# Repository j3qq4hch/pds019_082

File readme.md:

# PDS019_082

В этом репозитории лежат исходники устройства PDS019_082. Это контроллер, управляющий состоянием плавательного бассейна. 
Внешний вид представлен на картинке ниже:

> [!IMPORTANT]
> Исходная документация (включая производственную документацию) хранится [здесь](https://github.com/j3qq4hch/pds019_082/issues/1).

3d модель доступна [по ссылке](https://a360.co/41i2nmS).

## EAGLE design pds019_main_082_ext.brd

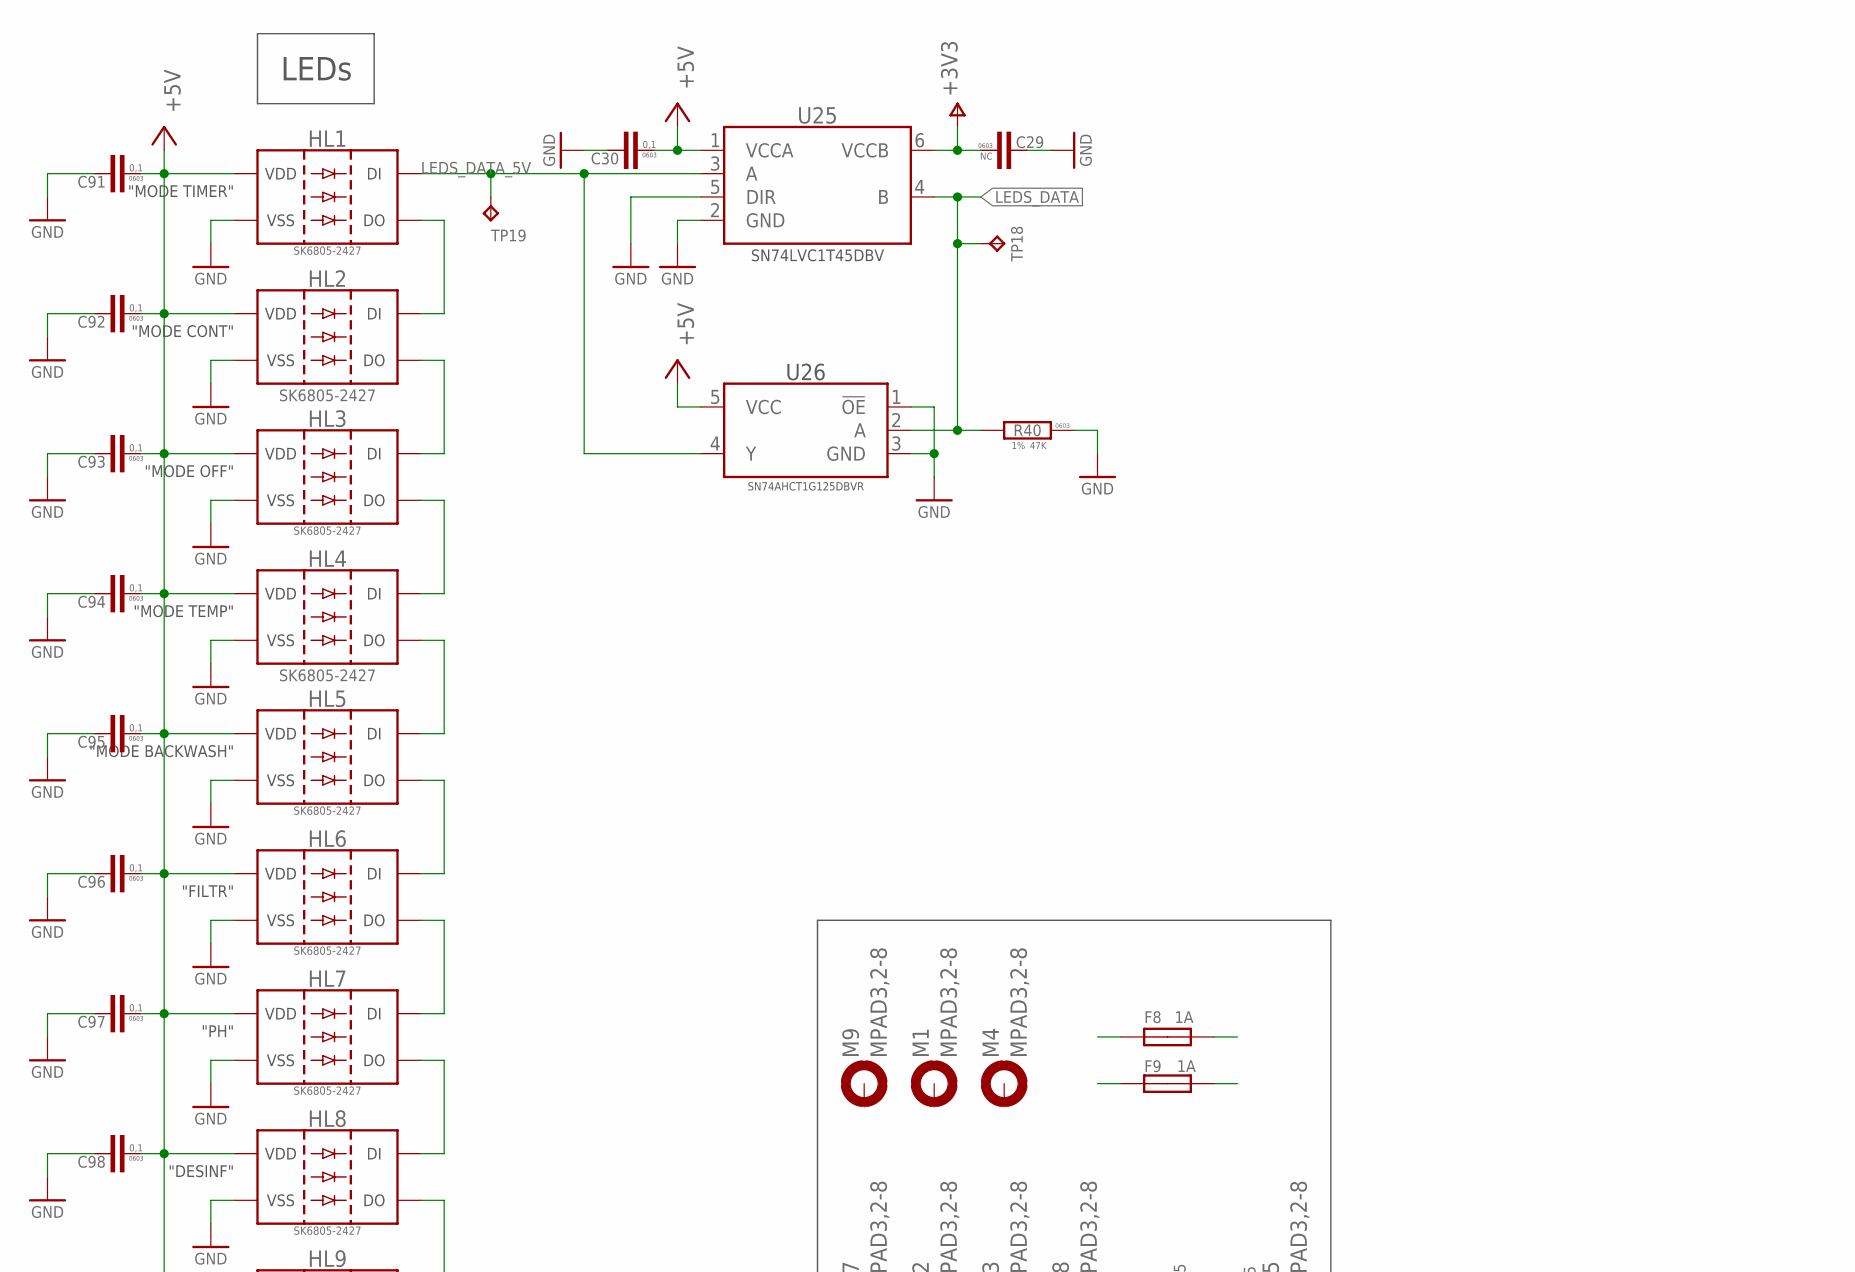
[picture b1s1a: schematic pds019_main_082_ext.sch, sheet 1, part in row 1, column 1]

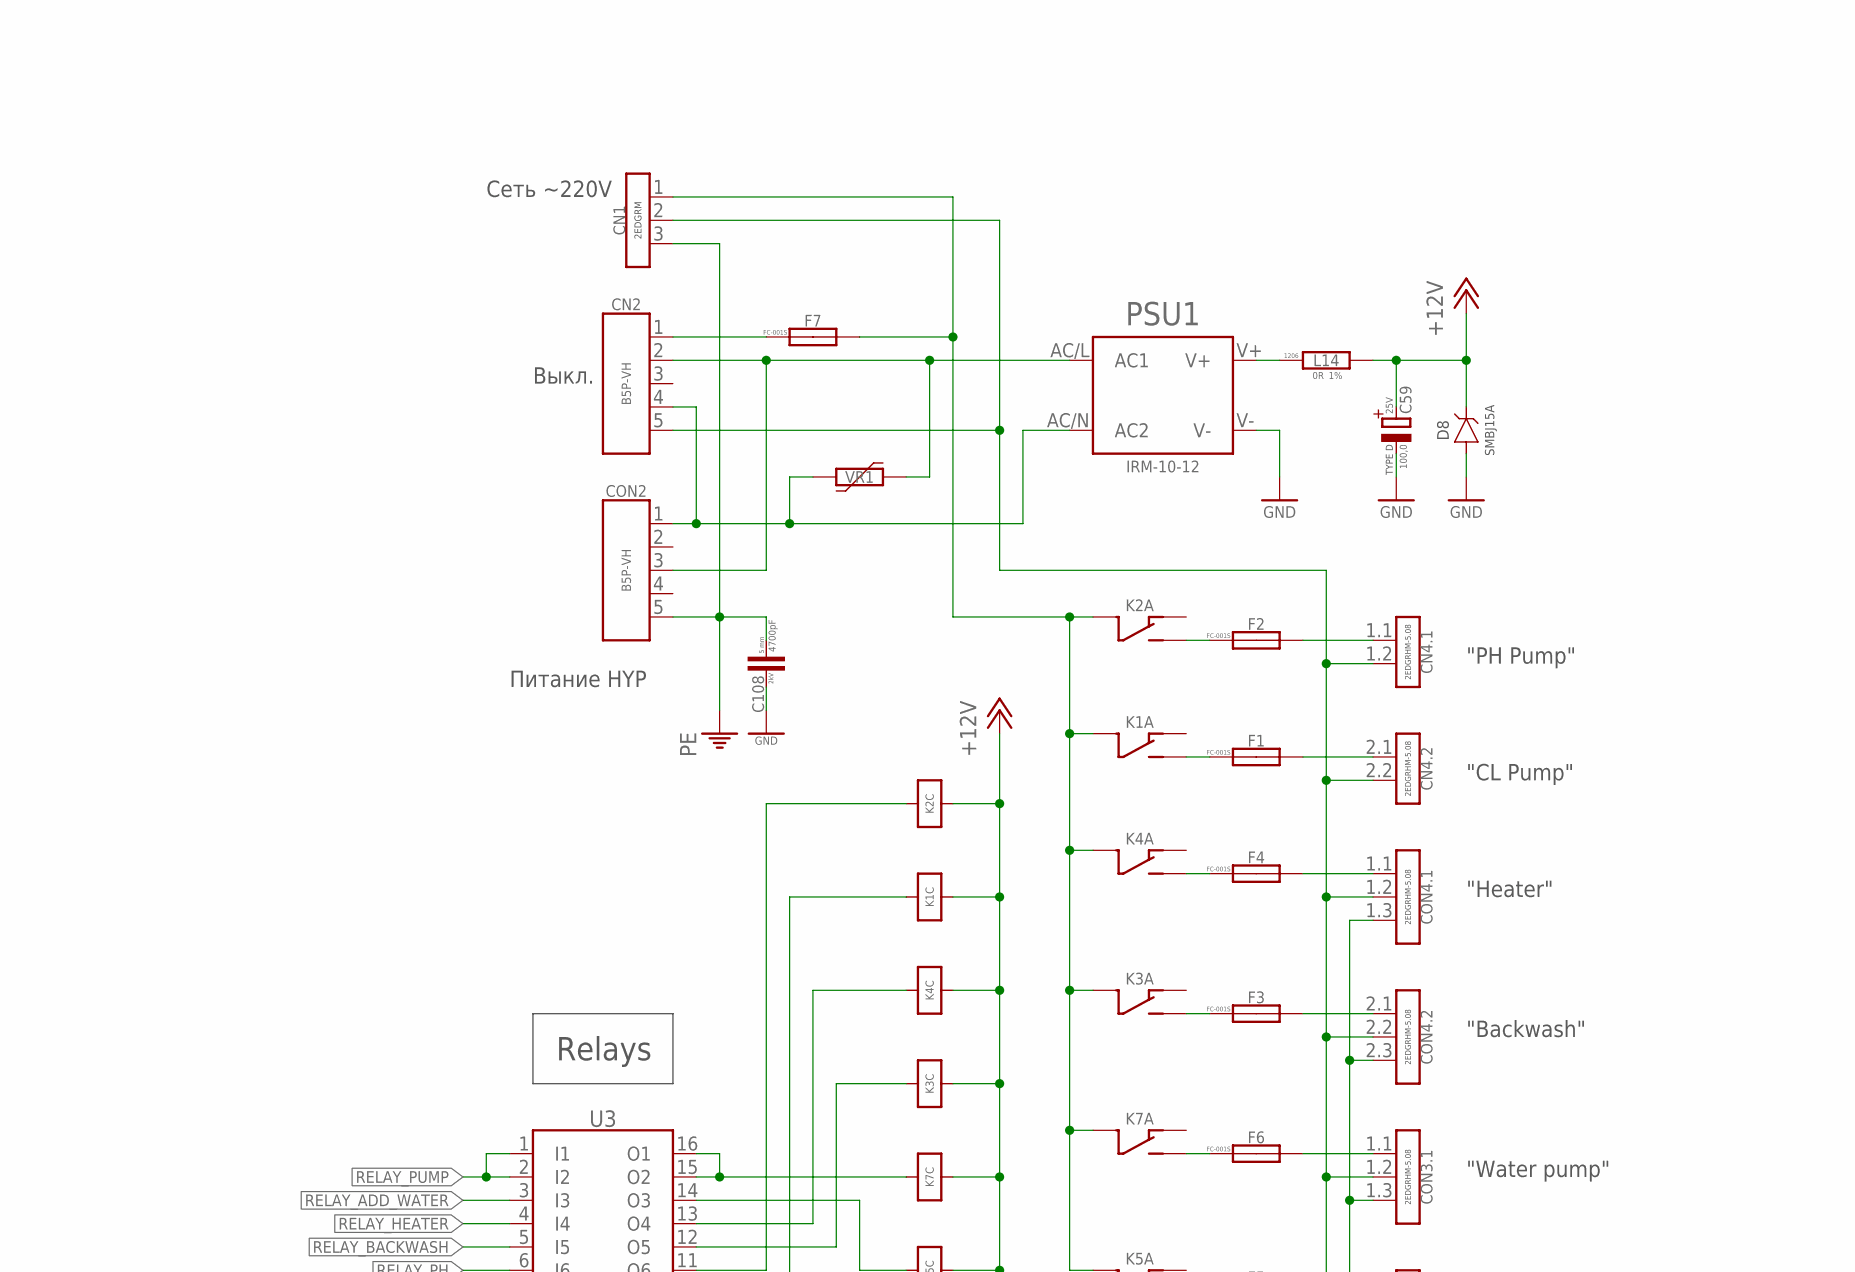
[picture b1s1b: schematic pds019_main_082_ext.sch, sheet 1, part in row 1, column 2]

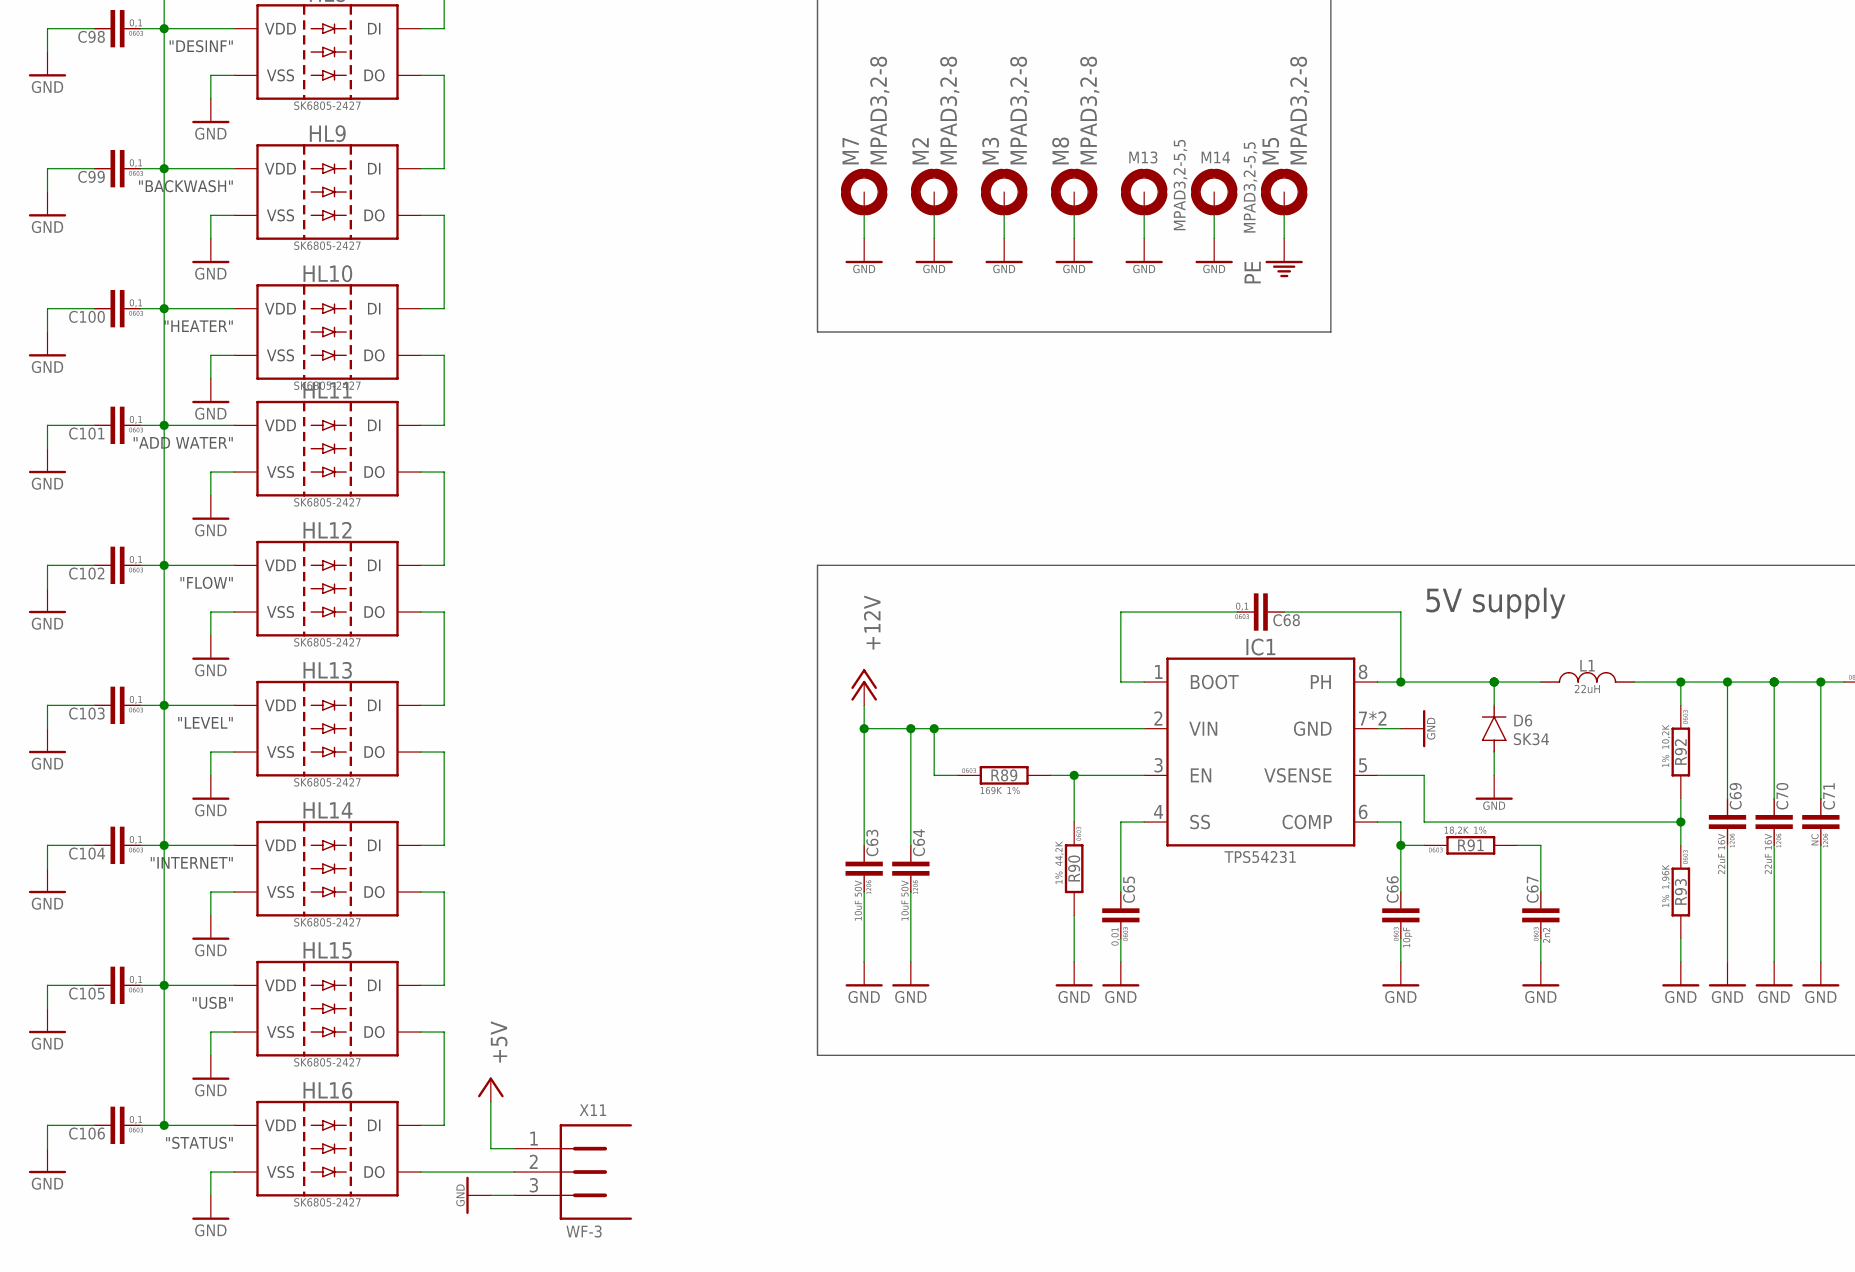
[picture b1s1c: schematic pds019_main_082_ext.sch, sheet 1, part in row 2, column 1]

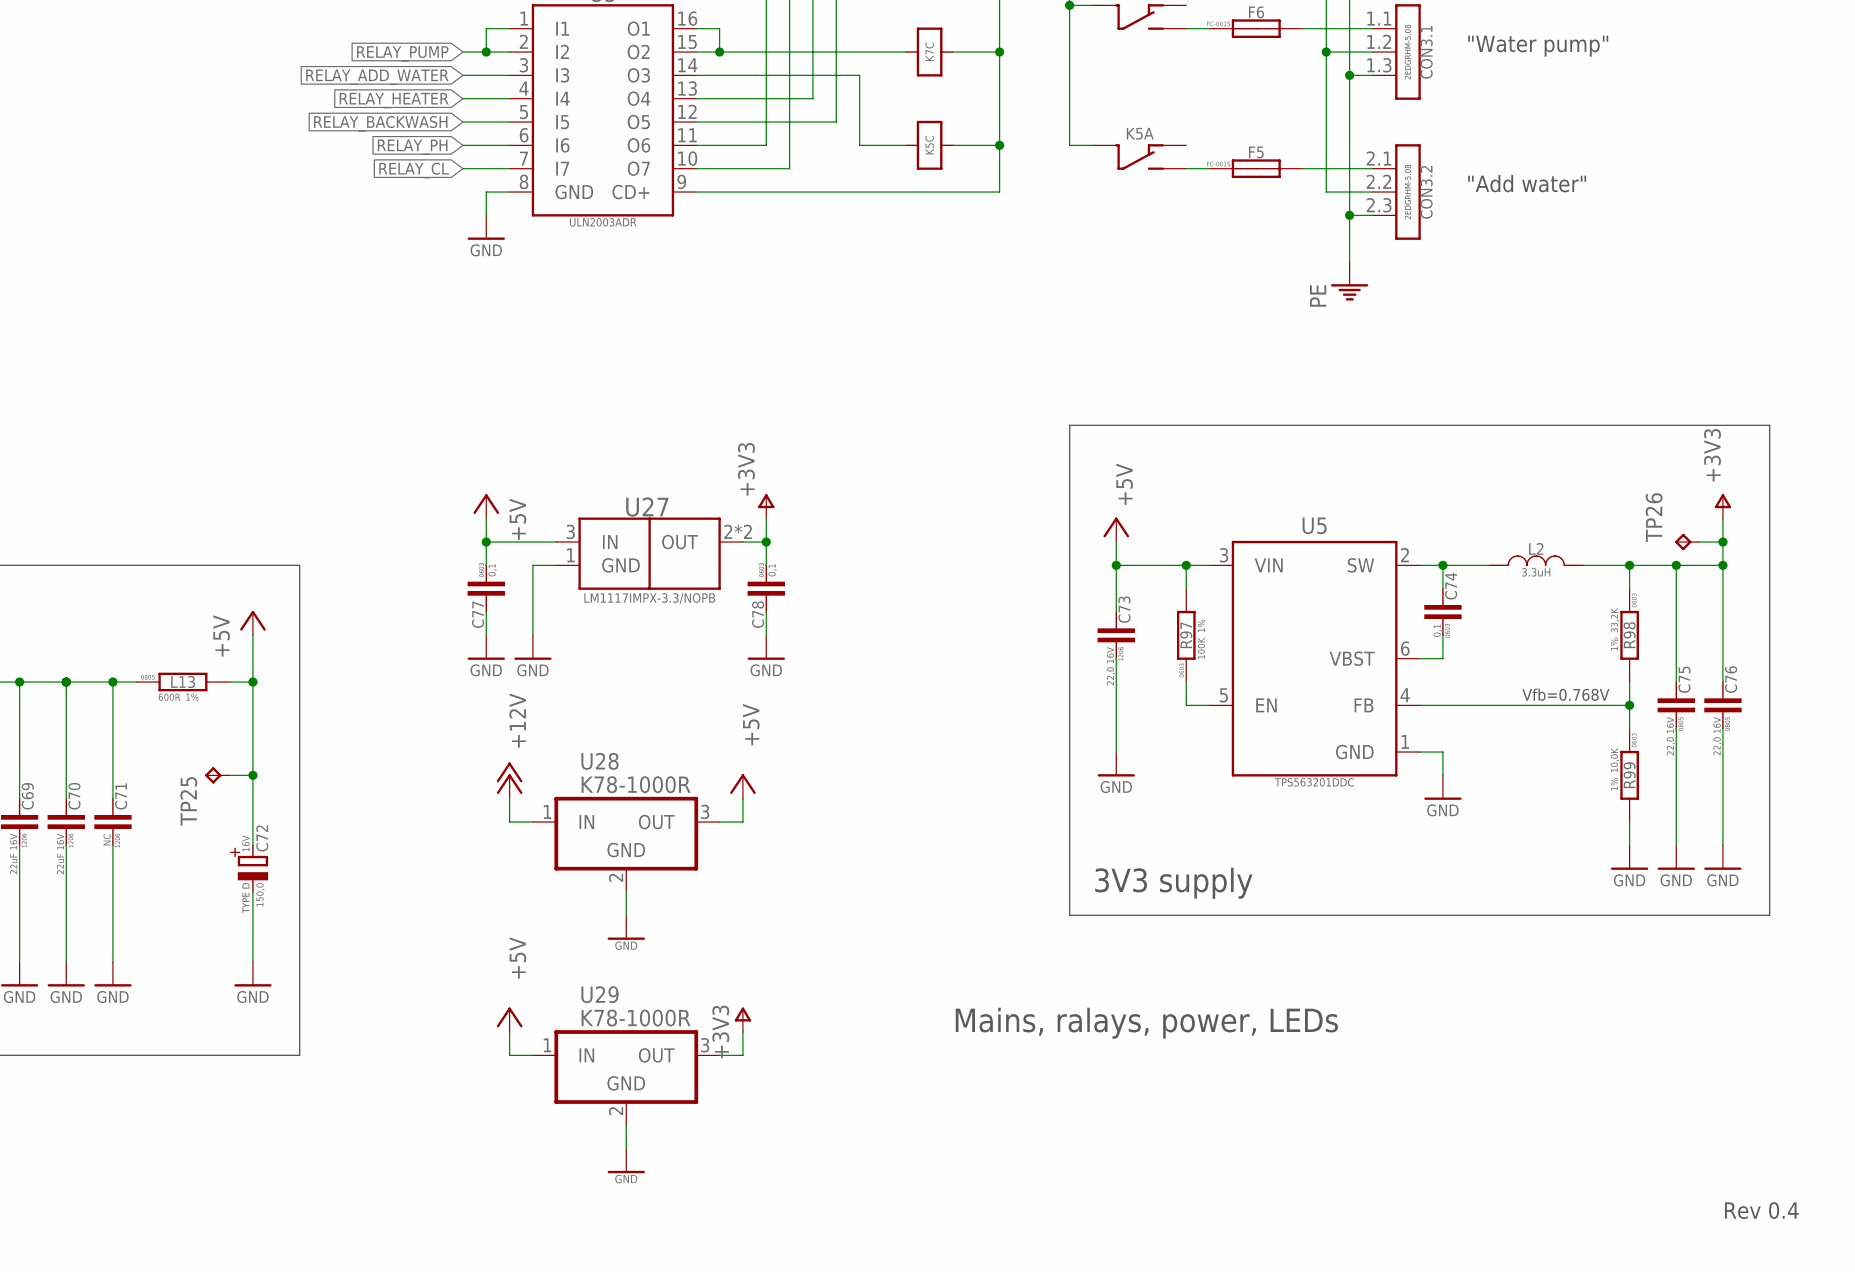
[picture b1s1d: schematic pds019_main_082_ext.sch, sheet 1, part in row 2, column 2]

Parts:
C29: NC; C0603
C30, C68, C74, C77, C78, C91, C92, C93, C94, C95, C96, C97, C98, C99, C100, C101, C102, C103, C104, C105, C106: 0,1; C0603
C59: 100,0; CTANT_7X4; VOLTAGE 25V
C63, C64: 10uF 50V; C1206
C65: 0,01; C0603
C66: 10pF; C0603
C67: 2n2; C0603
C69, C70: 22uF 16V; C1206
C71: NC; C1206
C72: 150,0; CTANT_7X4; VOLTAGE 16V
C73: 22,0 16V; C1206
C75, C76: 22,0 16V; C0805
C108: 4700pF; C_5MM; VOLTAGE 2kV
CN1: 2EDGRM-7.62-03P
CN2: CON-5P-JST-VH; B5P-VH
CN4: CON-2X2; 2EDGRHM-5.08-04P
CON2: CON-5P-JST-VH; B5P-VH
CON3, CON4: CON-2X3; 2EDGRHM-5.08-06P
D6: SK34; DO-214AC(SMA)
D8: SMBJ15A; DO-214AA(SMB)
F1, F2, F3, F4, F5, F6, F7, F8, F9: 1A; FC-001S
HL1, HL2, HL3, HL4, HL5, HL6, HL7, HL8, HL9, HL10, HL11, HL12, HL13, HL14, HL15, HL16: SK6805-2427
IC1: TPS54231; SOIC8-POWERPAD
K1, K2, K3, K4, K5: HLS8-22F-DC12V-C; SRD_UNIV
K7: SRD-SLC; SLC-12VDC-SL-C
L1: 22uH; LSMD_06030
L2: 3.3uH; LSMD_05020
L13: 600R; R0805
L14: 0R; R1206
M1, M2, M3, M4, M5, M7, M8, M9: MPAD3,2-8; MPAD_3,2_8
M13, M14: MPAD3,2-5,5; MPAD_3,2_5,5
PSU1: IRM-10-12; IRM-10
R40: 47K; R0603
R89: 169K; R0603
R90: 44,2K; R0603
R91: 18,2K; R0603
R92: 10,2K; R0603
R93: 1,96K; R0603
R97: 100K; R0603
R98: 33,2K; R0603
R99: 10,0K; R0603
TP18, TP19, TP25, TP26: TPTP16R; TP16R
U3: ULN2003AD; SO16
U5: TPS563201DDC; SOT23-6
U25: NC; SOT23-6
U26: SN74AHCT1G125DBVR-SOT23-5; SOT23-5
U27: 3.3V; SOT-223
U28, U29: K78-1000R; K78XX-1000R3_V
VR1: S20K275; S20K420
X11: WF-3; KF2510-03

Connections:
3V3_EN: R97.1, U5.5 (EN)
+3V3: C29.1, C75.2, C76.2, C78.1, L2.2, R98.1, TP26.TP, U25.6 (VCCB), U27.2 (OUT), U27.4 (OUT), U29.3 (OUT); also elsewhere on the board
+5V: C30.1, C72.+, C73.P$2 (2), C77.1, C91.1, C92.1, C93.1, C94.1, C95.1, C96.1, C97.1, C98.1, C99.1, C100.1, C101.1, C102.1, C103.1, C104.1, C105.1, C106.1, HL1.4 (VDD), HL2.4 (VDD), HL3.4 (VDD), HL4.4 (VDD), HL5.4 (VDD), HL6.4 (VDD), HL7.4 (VDD), HL8.4 (VDD), HL9.4 (VDD), HL10.4 (VDD), HL11.4 (VDD), HL12.4 (VDD), HL13.4 (VDD), HL14.4 (VDD), HL15.4 (VDD), HL16.4 (VDD), L13.2, R97.2, TP25.TP, U5.3 (VIN), U25.1 (VCCA), U26.5 (VCC), U27.3 (IN), U28.3 (OUT), U29.1 (IN), X11.1; also elsewhere on the board
+12V: C59.+, C63.P$2 (2), C64.P$2 (2), D8.C, IC1.2 (VIN), K1.2 (1), K2.2 (1), K3.2 (1), K4.2 (1), K5.2 (1), K7.C2 (2), L14.P$2 (2), R89.1, U3.9 (CD+), U28.1 (IN); also elsewhere on the board
AC_L: CN1.1, F7.2-1 (2), F7.2-2 (2), K1.1 (COM), K2.1 (COM), K3.1 (COM), K4.1 (COM), K5.1 (COM), K7.COM
AC_N: CN1.2, CN2.5, CN4.1.2 (2), CN4.2.2 (2), CON3.1.2 (2), CON3.2.2 (2), CON4.1.2 (2), CON4.2.2 (2)
F8-1: F8.1-1 (1), F8.1-2 (1)
F8-2: F8.2-1 (2), F8.2-2 (2)
F9-1: F9.1-1 (1), F9.1-2 (1)
F9-2: F9.2-1 (2), F9.2-2 (2)
GND: C29.2, C30.2, C59.-, C63.P$1 (1), C64.P$1 (1), C65.1, C66.1, C67.1, C69.P$1 (1), C70.P$1 (1), C71.P$1 (1), C72.-, C73.P$1 (1), C75.1, C76.1, C77.2, C78.2, C91.2, C92.2, C93.2, C94.2, C95.2, C96.2, C97.2, C98.2, C99.2, C100.2, C101.2, C102.2, C103.2, C104.2, C105.2, C106.2, C108.2, D6.A, D8.A, HL1.2 (VSS), HL2.2 (VSS), HL3.2 (VSS), HL4.2 (VSS), HL5.2 (VSS), HL6.2 (VSS), HL7.2 (VSS), HL8.2 (VSS), HL9.2 (VSS), HL10.2 (VSS), HL11.2 (VSS), HL12.2 (VSS), HL13.2 (VSS), HL14.2 (VSS), HL15.2 (VSS), HL16.2 (VSS), IC1.7 (GND), IC1.POWERPAD (GND), M2.1, M3.1, M7.1, M8.1, M13.1, M14.1, PSU1.V-, R40.1, R90.2, R93.2, R99.2, U3.8 (GND), U5.1 (GND), U25.2 (GND), U25.5 (DIR), U26.1 (!OE), U26.3 (GND), U27.1 (GND), U28.2 (GND), U29.2 (GND), X11.3; also elsewhere on the board
LED1_LED2: HL1.1 (DO), HL2.3 (DI)
LED2_LED3: HL2.1 (DO), HL3.3 (DI)
LED3_LED4: HL3.1 (DO), HL4.3 (DI)
LED4_LED5: HL4.1 (DO), HL5.3 (DI)
LED6_LED7: HL5.1 (DO), HL6.3 (DI)
LED7_LED8: HL7.1 (DO), HL8.3 (DI)
LED8_LED9: HL8.1 (DO), HL9.3 (DI)
LED9_LED10: HL9.1 (DO), HL10.3 (DI)
LED10_LED11: HL10.1 (DO), HL11.3 (DI)
LED11_LED12: HL11.1 (DO), HL12.3 (DI)
LED12_LED13: HL12.1 (DO), HL13.3 (DI)
LED13_LED14: HL13.1 (DO), HL14.3 (DI)
LED14_LED15: HL14.1 (DO), HL15.3 (DI)
LED15_LED16: HL15.1 (DO), HL16.3 (DI)
LEDS_DATA: R40.2, TP18.TP, U25.4 (B), U26.2 (A); also elsewhere on the board
LEDS_DATA_5V: HL1.3 (DI), TP19.TP, U25.3 (A), U26.4 (Y); also elsewhere on the board
unnamed: CN2.1, F7.1-1 (1), F7.1-2 (1)
unnamed: CN2.2, CON2.3, PSU1.AC/L (AC1), VR1.2
unnamed: CN2.4, CON2.1, PSU1.AC/N (AC2), VR1.1
unnamed: L14.P$1 (1), PSU1.V+
unnamed: C69.P$2 (2), C70.P$2 (2), C71.P$2 (2), L1.2, L13.1, R92.1
unnamed: K7.C1 (1), U3.15 (O2), U3.16 (O1)
unnamed: HL6.1 (DO), HL7.3 (DI)
unnamed: HL16.1 (DO), X11.2
unnamed: F2.1-1 (1), F2.1-2 (1), K2.3 (NO)
unnamed: C65.2, IC1.4 (SS)
unnamed: K2.5 (2), U3.11 (O6)
unnamed: K1.5 (2), U3.10 (O7)
unnamed: C68.1, IC1.1 (BOOT)
unnamed: K4.5 (2), U3.13 (O4)
unnamed: K3.5 (2), U3.12 (O5)
unnamed: K5.5 (2), U3.14 (O3)
unnamed: F6.1-1 (1), F6.1-2 (1), K7.NO
unnamed: C68.2, D6.C, IC1.8 (PH), L1.1
unnamed: C66.2, IC1.6 (COMP), R91.1
unnamed: C67.2, R91.2
unnamed: CN4.1.1 (1), F2.2-1 (2), F2.2-2 (2)
unnamed: CN4.2.1 (1), F1.2-1 (2), F1.2-2 (2)
unnamed: F1.1-1 (1), F1.1-2 (1), K1.3 (NO)
unnamed: CON4.1.1 (1), F4.2-1 (2), F4.2-2 (2)
unnamed: IC1.5 (VSENSE), R92.2, R93.1
unnamed: IC1.3 (EN), R89.2, R90.1
unnamed: F4.1-1 (1), F4.1-2 (1), K4.3 (NO)
unnamed: CON4.2.1 (1), F3.2-1 (2), F3.2-2 (2)
unnamed: F3.1-1 (1), F3.1-2 (1), K3.3 (NO)
unnamed: CON3.1.1 (1), F6.2-1 (2), F6.2-2 (2)
unnamed: F5.1-1 (1), F5.1-2 (1), K5.3 (NO)
unnamed: CON3.2.1 (1), F5.2-1 (2), F5.2-2 (2)
PE: C108.1, CN1.3, CON2.5, CON3.1.3 (3), CON3.2.3 (3), CON4.1.3 (3), CON4.2.3 (3), M5.1; also elsewhere on the board
RELAY_ADD_WATER: U3.3 (I3); also elsewhere on the board
RELAY_BACKWASH: U3.5 (I5); also elsewhere on the board
RELAY_CL: U3.7 (I7); also elsewhere on the board
RELAY_HEATER: U3.4 (I4); also elsewhere on the board
RELAY_PH: U3.6 (I6); also elsewhere on the board
RELAY_PUMP: U3.1 (I1), U3.2 (I2); also elsewhere on the board
TPS56_FB: R98.2, R99.1, U5.4 (FB)
TPS56_SW: C74.2, L2.1, U5.2 (SW)
TPS56_VBST: C74.1, U5.6 (VBST)

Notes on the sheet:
Сеть ~220V
"PH Pump"
"CL Pump"
Выкл.
Mains, ralays, power, LEDs
LEDs
Питание HYP
"Heater"
"Backwash"
"Water pump"
"Add water"
"MODE TIMER"
"MODE CONT"
"MODE OFF"
"MODE TEMP"
"MODE BACKWASH"
"FILTR"
"PH"
"DESINF"
"BACKWASH"
"HEATER"
"ADD WATER"
"FLOW"
"LEVEL"
"INTERNET"
"USB"
"STATUS"
Rev 0.4
5V supply
3V3 supply
Relays
Vfb=0.768V
